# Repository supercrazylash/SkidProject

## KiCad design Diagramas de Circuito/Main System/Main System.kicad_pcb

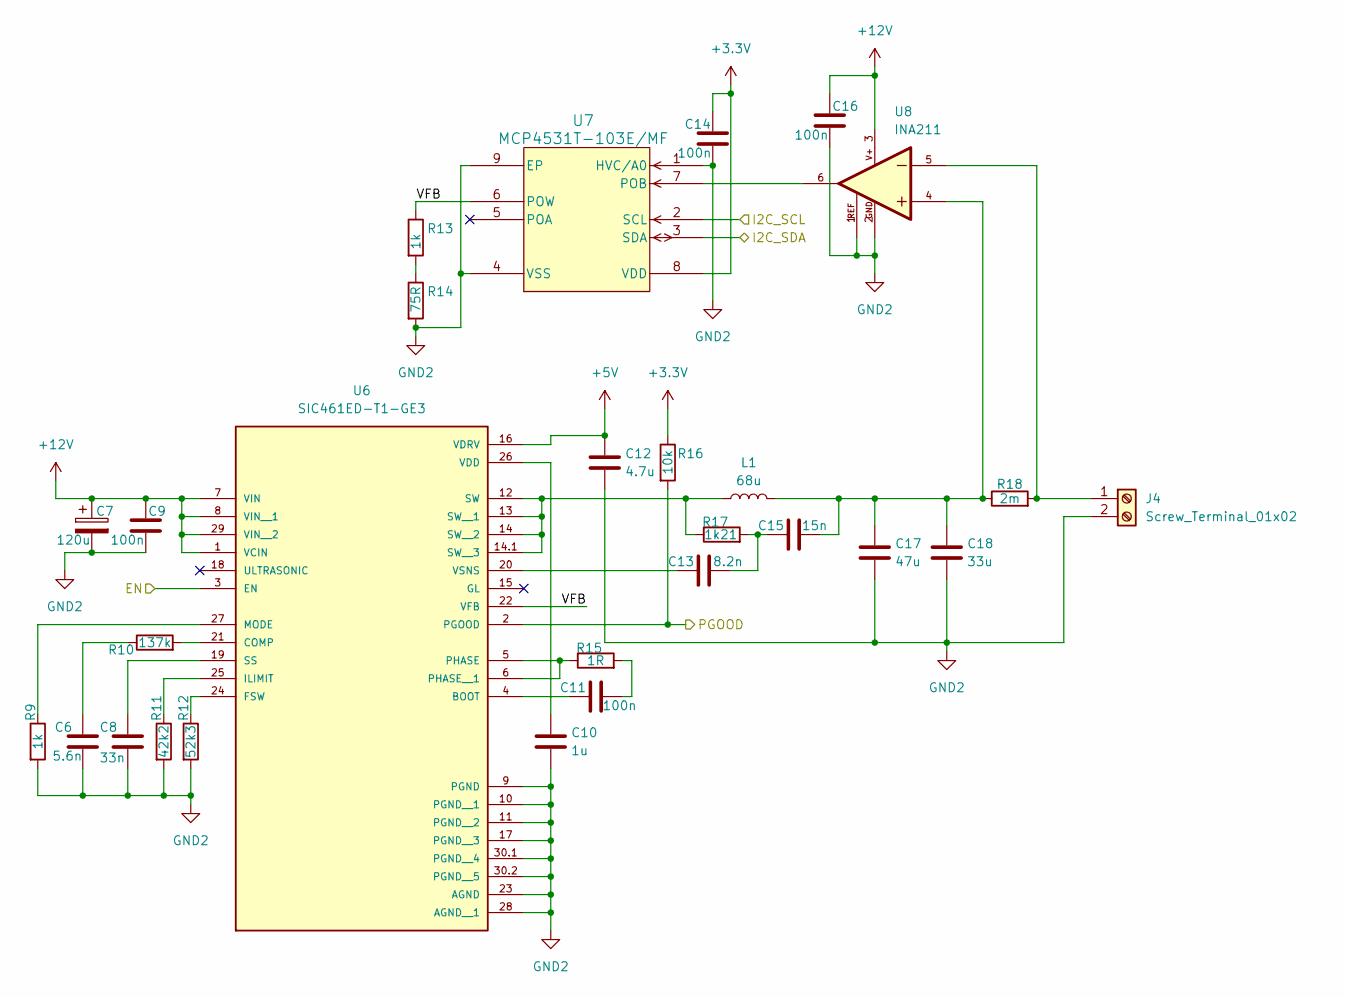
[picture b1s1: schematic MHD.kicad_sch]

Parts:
C6: 5.6n; C_0402_1005Metric; DIGIKEY_PN 311-3773-1-ND
C7: 120u; CP_Radial_D10.0mm_P5.00mm; DIGIKEY_PN 732-11923-1-ND
C8: 33n; C_0402_1005Metric; DIGIKEY_PN 13-CC0402JRX7R9BB333CT-ND
C9, C11, C14, C16: 100n; C_0603_1608Metric; DIGIKEY_PN 1276-1033-1-ND
C10: 1u; C_0805_2012Metric; DIGIKEY_PN 1276-1029-1-ND
C12: 4.7u; C_0603_1608Metric; DIGIKEY_PN 1276-1784-1-ND
C13: 8.2n; C_0603_1608Metric; DIGIKEY_PN 399-C0603C822K5RACTUCT-ND
C15: 15n; C_0402_1005Metric; DIGIKEY_PN 311-3813-1-ND
C17: 47u; C_1210_3225Metric; DIGIKEY_PN 490-10531-1-ND
C18: 33u; C_1206_3216Metric; DIGIKEY_PN 4713-GMC31X5R336M25NTCT-ND
J4: Screw_Terminal_01x02; TerminalBlock_Phoenix_PT-1,5-2-5.0-H_1x02_P5.00mm_Horizontal; DIGIKEY_PN 277-1667-ND
L1: 68u; L_Pulse_PA4349; DIGIKEY_PN 553-PA4349.683ANLTCT-ND
R9, R13: 1k; R_0402_1005Metric; DIGIKEY_PN P1.0KDCCT-ND
R10: 137k; R_0402_1005Metric; DIGIKEY_PN P137KLCT-ND
R11: 42k2; R_0402_1005Metric; DIGIKEY_PN 311-42.2KLRCT-ND
R12: 52k3; R_0402_1005Metric; DIGIKEY_PN P52.3KLCT-ND
R14: 75R; R_0402_1005Metric; DIGIKEY_PN P75.0LCT-ND
R15: 1R; R_0603_1608Metric; DIGIKEY_PN 311-1.00HRCT-ND
R16: 10k; R_0603_1608Metric; DIGIKEY_PN RMCF0603JT10K0CT-ND
R17: 1k21; R_0402_1005Metric; DIGIKEY_PN P1.21KLCT-ND
R18: 2m; R_2512_6332Metric; DIGIKEY_PN 13-PA2512DKF7W0R002ECT-ND
U6: SIC461ED-T1-GE3; CONV_SIC461ED-T1-GE3; PARTREV M; DIGIKEY_PN SIC461ED-T1-GE3CT-ND
U7: MCP4531T-103E/MF; DFN-8-1EP_3x3mm_P0.5mm_EP1.65x2.38mm; DIGIKEY_PN MCP4531T-103E/MFCT-ND
U8: INA211; SOT-363_SC-70-6; PARTREV J; DIGIKEY_PN 296-41417-1-ND

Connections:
+3.3V: C14.1, R16.1, U7.8 (VDD); also elsewhere on the board
+5V: C12.1, U6.16 (VDRV); also elsewhere on the board
+12V: C7.1, C9.1, C16.1, U6.1 (VCIN), U6.7 (VIN), U6.8 (VIN__1), U6.29 (VIN__2), U8.3; also elsewhere on the board
/Magneto-Hidrodynamic Drive/EN: U6.3 (EN); also elsewhere on the board
/Magneto-Hidrodynamic Drive/PGOOD: R16.2, U6.2 (PGOOD); also elsewhere on the board
/Magneto-Hidrodynamic Drive/VFB: R13.1, U6.22 (VFB), U7.6 (POW)
/Processor/I2C_SCL: U7.2 (SCL); also elsewhere on the board
/Processor/I2C_SDA: U7.3 (SDA); also elsewhere on the board
GND2: C6.2, C7.2, C8.2, C9.2, C10.2, C12.2, C14.2, C16.2, C17.2, C18.2, J4.2, R9.2, R11.2, R12.2, R14.2, U6.9 (PGND), U6.10 (PGND__1), U6.11 (PGND__2), U6.17 (PGND__3), U6.23 (AGND), U6.28 (AGND__1), U6.30.1 (PGND__4), U6.30.2 (PGND__5), U7.1 (HVC/A0), U7.4 (VSS), U7.9 (EP), U8.1, U8.2; also elsewhere on the board
unnamed: C6.1, R10.1
unnamed: C11.2, R15.2
unnamed: C13.2, C15.1, R17.2
unnamed: C15.2, C17.1, C18.1, L1.2, R18.1, U8.4
unnamed: J4.1, R18.2, U8.5
unnamed: R13.2, R14.1
unnamed: C11.1, U6.4 (BOOT)
unnamed: R10.2, U6.21 (COMP)
unnamed: R12.1, U6.24 (FSW)
unnamed: R11.1, U6.25 (ILIMIT)
unnamed: R9.1, U6.27 (MODE)
unnamed: R15.1, U6.5 (PHASE), U6.6 (PHASE__1)
unnamed: C8.1, U6.19 (SS)
unnamed: L1.1, R17.1, U6.12 (SW), U6.13 (SW__1), U6.14 (SW__2), U6.14.1 (SW__3)
unnamed: C10.1, U6.26 (VDD)
unnamed: C13.1, U6.20 (VSNS)
unnamed: U7.7 (POB), U8.6

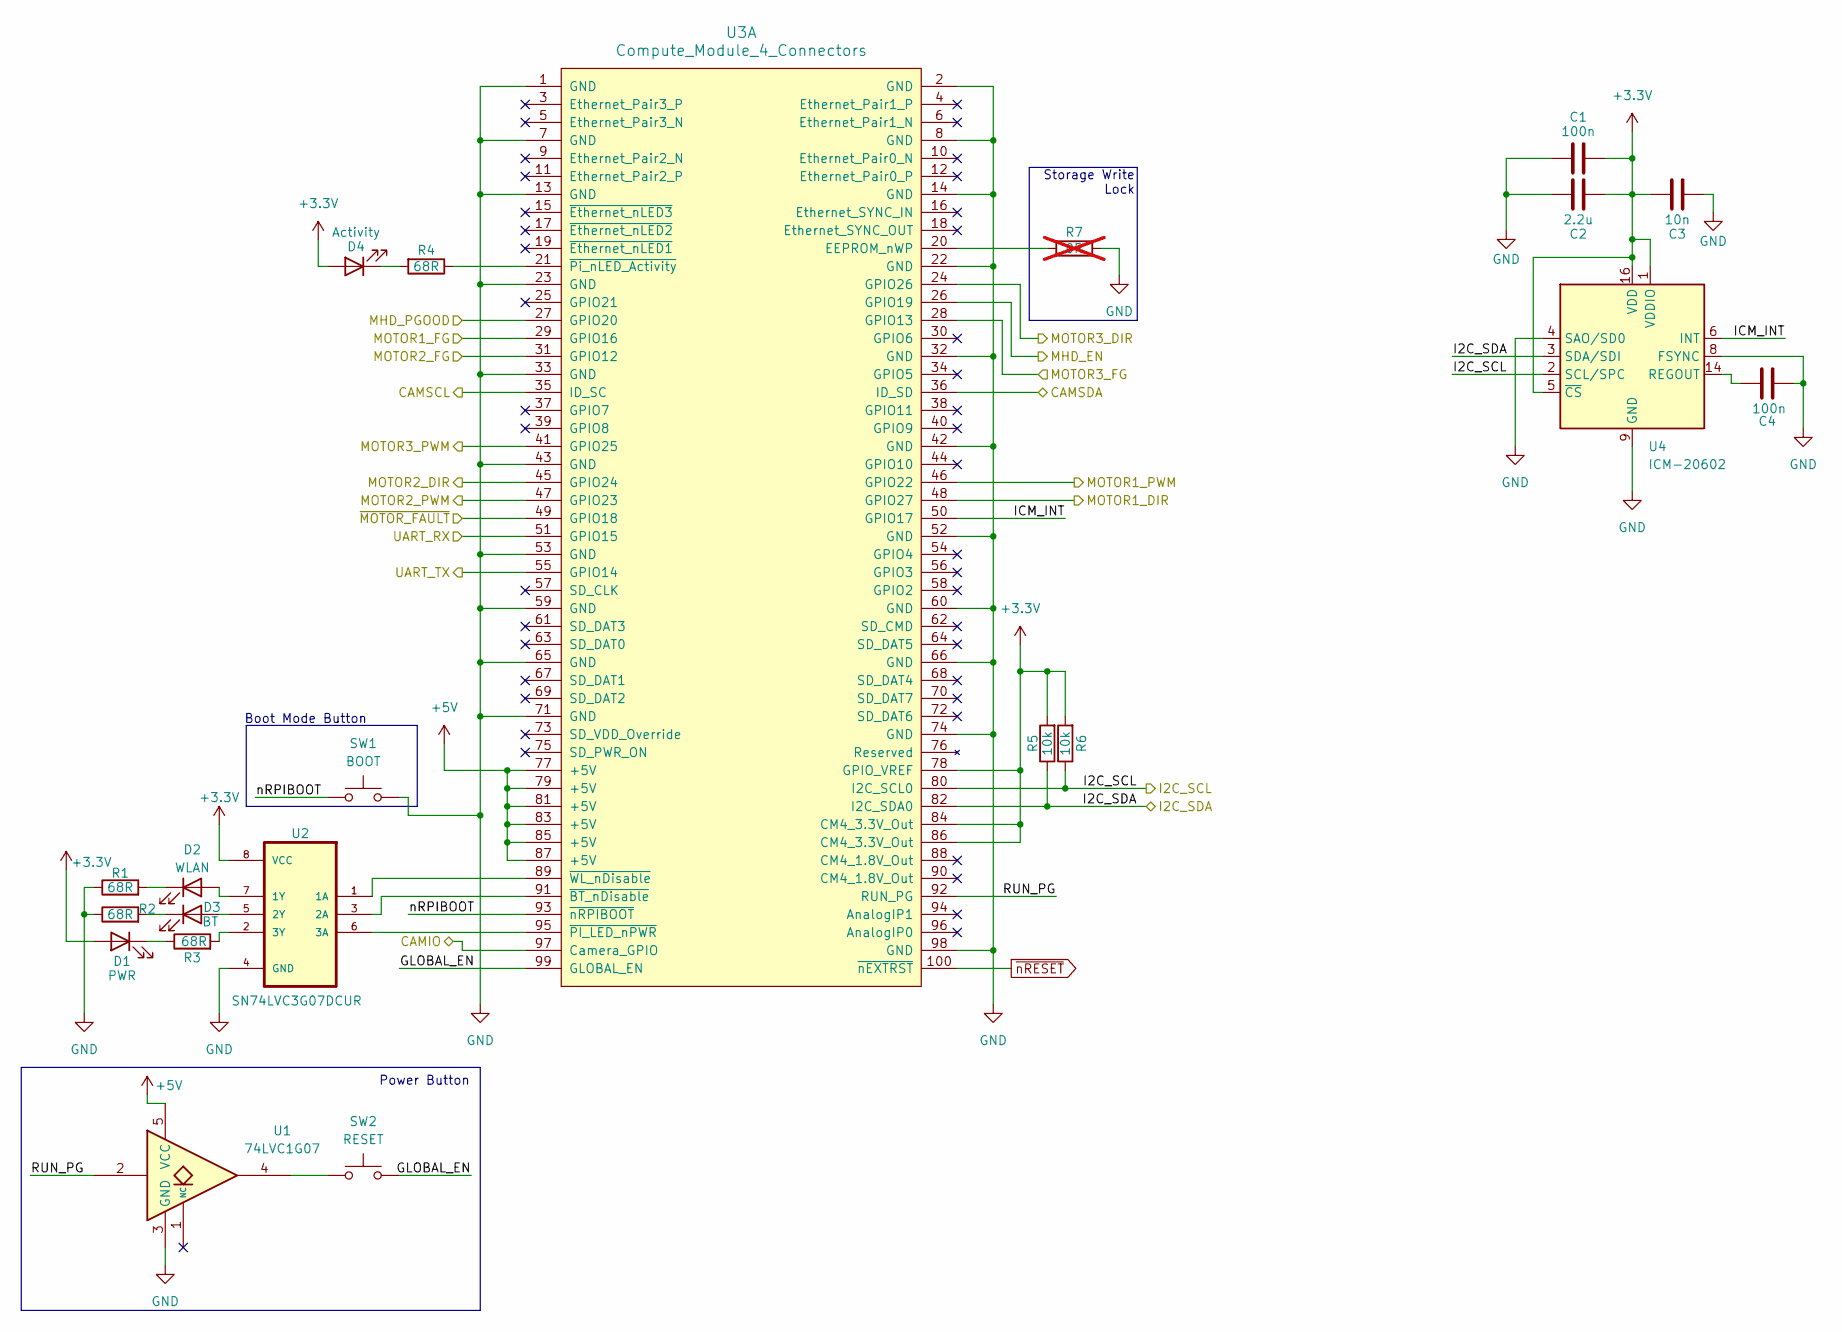
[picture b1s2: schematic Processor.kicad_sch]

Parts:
C1, C4: 100n; C_0603_1608Metric; DIGIKEY_PN 1276-1033-1-ND
C2: 2.2u; C_0603_1608Metric; DIGIKEY_PN 1276-1040-1-ND
C3: 10n; C_0402_1005Metric; DIGIKEY_PN 1276-1028-1-ND
D1: PWR; LED_0603_1608Metric; DIGIKEY_PN 732-4978-1-ND
D2: WLAN; LED_0603_1608Metric; DIGIKEY_PN 732-4980-1-ND
D3: BT; LED_0603_1608Metric; DIGIKEY_PN 732-4980-1-ND
D4: Activity; LED_0603_1608Metric; DIGIKEY_PN 732-4980-1-ND
R1, R2, R3, R4: 68R; R_0402_1005Metric; DIGIKEY_PN P68.0LCT-ND
R5, R6: 10k; R_0603_1608Metric; DIGIKEY_PN RMCF0603JT10K0CT-ND
R7: 0R; R_0402_1005Metric; DIGIKEY_PN P0.0JCT-ND; not fitted
SW1: BOOT; SW_SPST_PTS647_Sx38; DIGIKEY_PN PTS647SM38SMTR2LFSCT-ND
SW2: RESET; SW_SPST_PTS647_Sx38; DIGIKEY_PN PTS647SM38SMTR2LFSCT-ND
U1: 74LVC1G07; SOT-23-5; DIGIKEY_PN 296-8485-1-ND
U2: SN74LVC3G07DCUR; VSSOP-8_2.3x2mm_P0.5mm; DIGIKEY_PN 296-13283-1-ND
U3: Compute_Module_4_Connectors; Raspberry-Pi-4-Compute-Module; DIGIKEY_PN H11615CT-ND
U4: ICM-20602; LGA-16_3x3mm_P0.5mm_LayoutBorder3x5y; DIGIKEY_PN 1428-1060-1-ND

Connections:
+3.3V: C1.2, C2.2, C3.1, D1.2 (A), D4.2 (A), R5.2, R6.2, U2.8 (VCC), U3.78 (GPIO_VREF), U3.84 (CM4_3.3V_Out), U3.86 (CM4_3.3V_Out), U4.1 (VDDIO), U4.5 (~CS), U4.16 (VDD); also elsewhere on the board
+5V: U1.5 (VCC), U3.77 (+5V), U3.79 (+5V), U3.81 (+5V), U3.83 (+5V), U3.85 (+5V), U3.87 (+5V); also elsewhere on the board
/High Speed IO/CAMIO: U3.97 (Camera_GPIO); also elsewhere on the board
/High Speed IO/CAMSCL: U3.35 (ID_SC); also elsewhere on the board
/High Speed IO/CAMSDA: U3.36 (ID_SD); also elsewhere on the board
/High Speed IO/UART_RX: U3.55 (GPIO14); also elsewhere on the board
/High Speed IO/UART_TX: U3.51 (GPIO15); also elsewhere on the board
/Magneto-Hidrodynamic Drive/EN: U3.26 (GPIO19); also elsewhere on the board
/Magneto-Hidrodynamic Drive/PGOOD: U3.27 (GPIO20); also elsewhere on the board
/Processor/GLOBAL_EN: SW2.2, U3.99 (GLOBAL_EN)
/Processor/I2C_SCL: R6.1, U3.80 (I2C_SCL0), U4.2 (SCL/SPC); also elsewhere on the board
/Processor/I2C_SDA: R5.1, U3.82 (I2C_SDA0), U4.3 (SDA/SDI); also elsewhere on the board
/Processor/ICM_INT: U3.50 (GPIO17), U4.6 (INT)
/Processor/MOTOR1_DIR: U3.48 (GPIO27); also elsewhere on the board
/Processor/MOTOR1_FG: U3.29 (GPIO16); also elsewhere on the board
/Processor/MOTOR1_PWM: U3.46 (GPIO22); also elsewhere on the board
/Processor/MOTOR2_DIR: U3.45 (GPIO24); also elsewhere on the board
/Processor/MOTOR2_FG: U3.31 (GPIO12); also elsewhere on the board
/Processor/MOTOR2_PWM: U3.47 (GPIO23); also elsewhere on the board
/Processor/MOTOR3_DIR: U3.24 (GPIO26); also elsewhere on the board
/Processor/MOTOR3_FG: U3.28 (GPIO13); also elsewhere on the board
/Processor/MOTOR3_PWM: U3.41 (GPIO25); also elsewhere on the board
/Processor/RUN_PG: U1.2, U3.92 (RUN_PG)
/Processor/nRPIBOOT: SW1.1, U3.93 (~nRPIBOOT)
/Processor/~MOTOR_FAULT: U3.49 (GPIO18); also elsewhere on the board
GND: C1.1, C2.1, C3.2, C4.2, R1.1, R2.1, R7.2, SW1.2, U1.3 (GND), U2.4 (GND), U3.1 (GND), U3.2 (GND), U3.7 (GND), U3.8 (GND), U3.13 (GND), U3.14 (GND), U3.22 (GND), U3.23 (GND), U3.32 (GND), U3.33 (GND), U3.42 (GND), U3.43 (GND), U3.52 (GND), U3.53 (GND), U3.59 (GND), U3.60 (GND), U3.65 (GND), U3.66 (GND), U3.71 (GND), U3.74 (GND), U3.98 (GND), U4.4 (SAO/SD0), U4.8 (FSYNC), U4.9 (GND), U4.10 (GND), U4.11 (GND), U4.12 (GND), U4.13 (GND), U4.15 (GND); also elsewhere on the board
unnamed: D1.1 (K), R3.1
unnamed: D2.2 (A), U2.7 (1Y)
unnamed: D2.1 (K), R1.2
unnamed: D3.2 (A), U2.5 (2Y)
unnamed: D3.1 (K), R2.2
unnamed: D4.1 (K), R4.2
unnamed: SW2.1, U1.4
unnamed: U2.1 (1A), U3.89 (~WL_nDisable)
unnamed: U2.3 (2A), U3.91 (~BT_nDisable)
unnamed: U2.6 (3A), U3.95 (~PI_LED_nPWR)
unnamed: R3.2, U2.2 (3Y)
unnamed: R7.1, U3.20 (EEPROM_nWP)
unnamed: R4.1, U3.21 (~Pi_nLED_Activity)
unnamed: C4.1, U4.14 (REGOUT)
~nRESET: U3.100 (~nEXTRST); also elsewhere on the board

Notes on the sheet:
Storage Write Lock
Power Button
Boot Mode Button

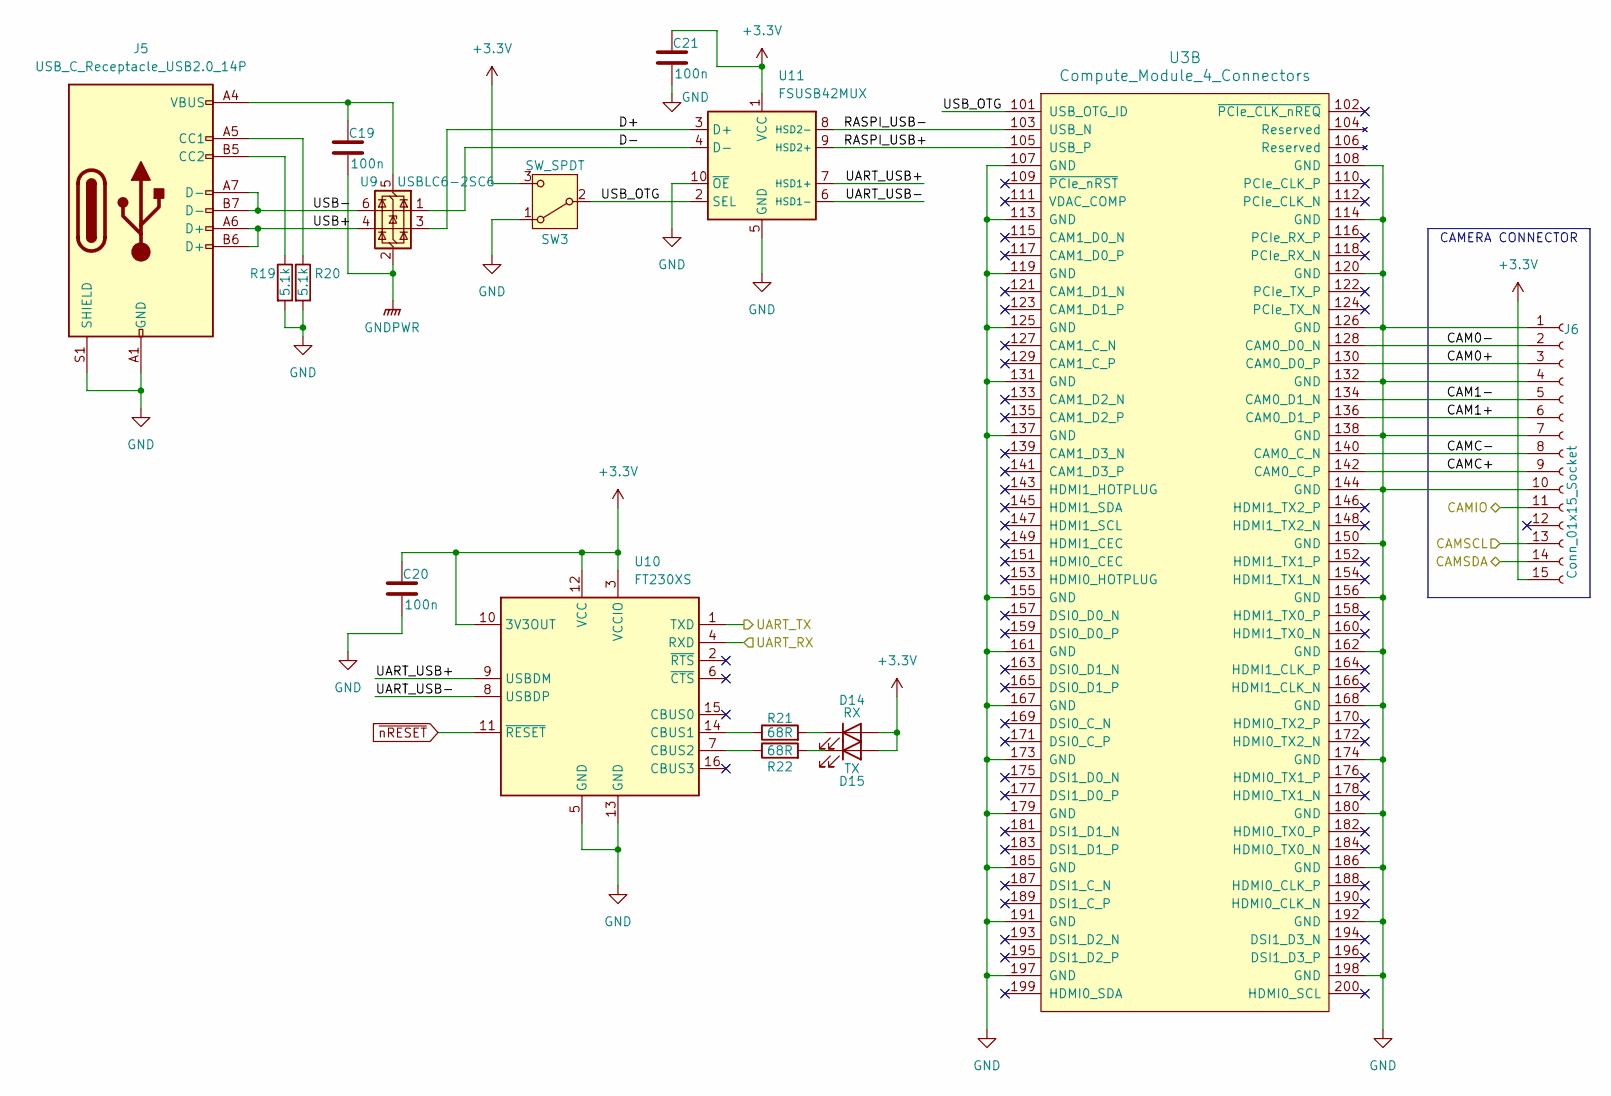
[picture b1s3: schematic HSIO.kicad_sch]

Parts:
C19, C20, C21: 100n; C_0603_1608Metric; DIGIKEY_PN 1276-1033-1-ND
D14: RX; LED_0603_1608Metric; DIGIKEY_PN 732-4980-1-ND
D15: TX; LED_0603_1608Metric; DIGIKEY_PN 732-4980-1-ND
J5: USB_C_Receptacle_USB2.0_14P; USB4120-03-C_GCT; DIGIKEY_PN 2073-USB4120-03-CCT-ND
J6: Conn_01x15_Socket; GCT_FFC3A20-15-G_REVA1; DIGIKEY_PN 2073-FFC3A20-15-GCT-ND
R19, R20: 5.1k; R_0402_1005Metric; DIGIKEY_PN P5.10KLCT-ND
R21, R22: 68R; R_0402_1005Metric; DIGIKEY_PN P68.0LCT-ND
SW3: SW_SPDT; SW_JS102011JCQN; DIGIKEY_PN CKN10721CT-ND
U3: Compute_Module_4_Connectors; Raspberry-Pi-4-Compute-Module; DIGIKEY_PN H11615CT-ND
U9: USBLC6-2SC6; SOT-23-6; DIGIKEY_PN 497-5235-1-ND
U10: FT230XS; SSOP-16_3.9x4.9mm_P0.635mm; DIGIKEY_PN 768-1135-1-ND
U11: FSUSB42MUX; MSOP-10_3x3mm_P0.5mm; DIGIKEY_PN FSUSB42MUXCT-ND

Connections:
+3.3V: C20.1, C21.1, D14.2 (A), D15.2 (A), J6.15, SW3.3 (C), U10.3 (VCCIO), U10.10 (3V3OUT), U10.12 (VCC), U11.1 (VCC); also elsewhere on the board
/High Speed IO/CAM0+: J6.3, U3.130 (CAM0_D0_P)
/High Speed IO/CAM0-: J6.2, U3.128 (CAM0_D0_N)
/High Speed IO/CAM1+: J6.6, U3.136 (CAM0_D1_P)
/High Speed IO/CAM1-: J6.5, U3.134 (CAM0_D1_N)
/High Speed IO/CAMC+: J6.9, U3.142 (CAM0_C_P)
/High Speed IO/CAMC-: J6.8, U3.140 (CAM0_C_N)
/High Speed IO/CAMIO: J6.11; also elsewhere on the board
/High Speed IO/CAMSCL: J6.13; also elsewhere on the board
/High Speed IO/CAMSDA: J6.14; also elsewhere on the board
/High Speed IO/D+: U9.3 (I/O2), U11.3 (D+)
/High Speed IO/D-: U9.1 (I/O1), U11.4 (D-)
/High Speed IO/RASPI_USB+: U3.105 (USB_P), U11.9 (HSD2+)
/High Speed IO/RASPI_USB-: U3.103 (USB_N), U11.8 (HSD2-)
/High Speed IO/UART_RX: U10.4 (RXD); also elsewhere on the board
/High Speed IO/UART_TX: U10.1 (TXD); also elsewhere on the board
/High Speed IO/UART_USB+: U10.9 (USBDM), U11.7 (HSD1+)
/High Speed IO/UART_USB-: U10.8 (USBDP), U11.6 (HSD1-)
/High Speed IO/USB+: J5.A6 (D+), J5.B6 (D+), U9.4 (I/O2)
/High Speed IO/USB-: J5.A7 (D-), J5.B7 (D-), U9.6 (I/O1)
/High Speed IO/USB_OTG: SW3.2 (B), U3.101 (USB_OTG_ID), U11.2 (SEL)
GND: C20.2, C21.2, J5.A1 (GND), J5.A12 (GND), J5.B1 (GND), J5.B12 (GND), J5.S1 (SHIELD), J6.1, J6.4, J6.7, J6.10, R19.2, R20.2, SW3.1 (A), U3.107 (GND), U3.108 (GND), U3.113 (GND), U3.114 (GND), U3.119 (GND), U3.120 (GND), U3.125 (GND), U3.126 (GND), U3.131 (GND), U3.132 (GND), U3.137 (GND), U3.138 (GND), U3.144 (GND), U3.150 (GND), U3.155 (GND), U3.156 (GND), U3.161 (GND), U3.162 (GND), U3.167 (GND), U3.168 (GND), U3.173 (GND), U3.174 (GND), U3.179 (GND), U3.180 (GND), U3.185 (GND), U3.186 (GND), U3.191 (GND), U3.192 (GND), U3.197 (GND), U3.198 (GND), U10.5 (GND), U10.13 (GND), U11.5 (GND), U11.10 (~OE); also elsewhere on the board
GNDPWR: C19.2, U9.2 (GND); also elsewhere on the board
unnamed: D14.1 (K), R21.2
unnamed: D15.1 (K), R22.2
unnamed: J5.A5 (CC1), R20.1
unnamed: J5.B5 (CC2), R19.1
unnamed: C19.1, J5.A4 (VBUS), J5.A9 (VBUS), J5.B4 (VBUS), J5.B9 (VBUS), U9.5 (VBUS)
unnamed: R21.1, U10.14 (CBUS1)
unnamed: R22.1, U10.7 (CBUS2)
~nRESET: U10.11 (~RESET); also elsewhere on the board

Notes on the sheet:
CAMERA CONNECTOR

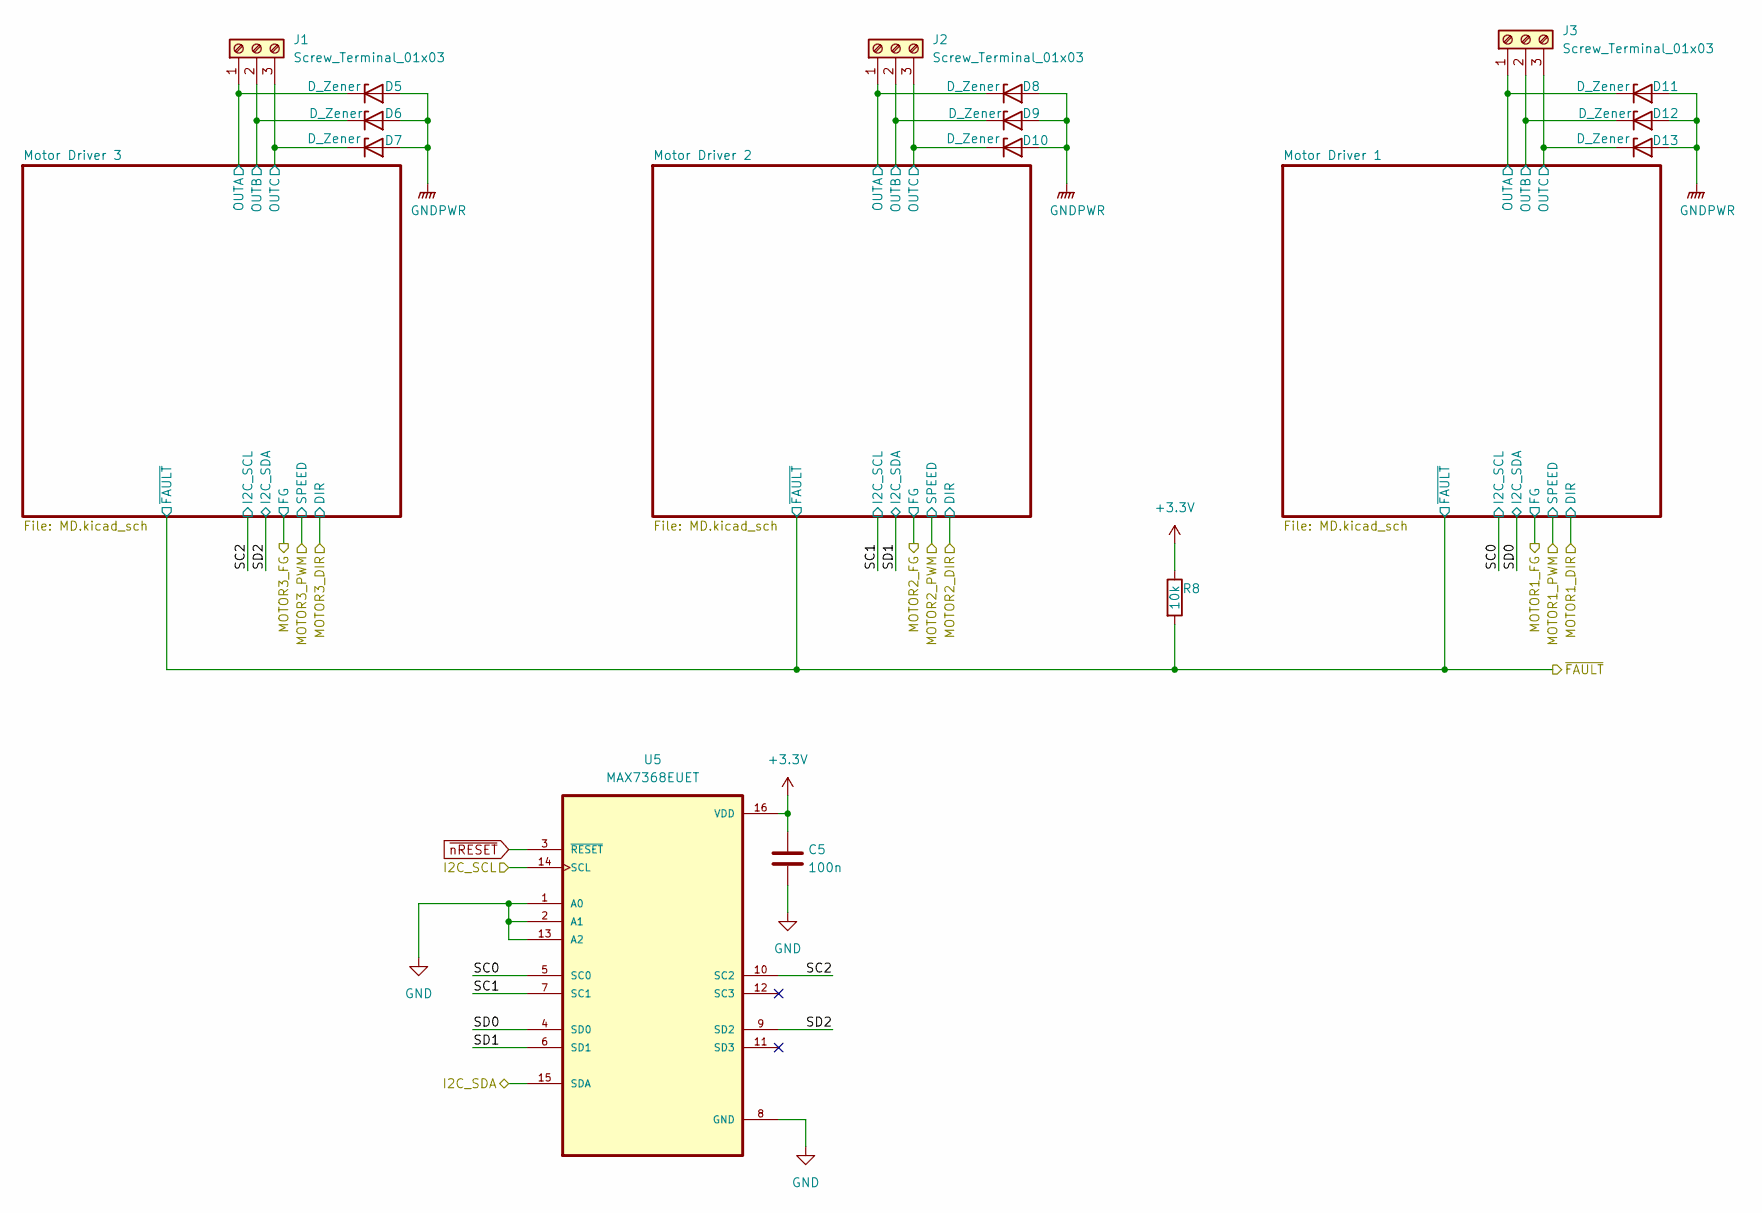
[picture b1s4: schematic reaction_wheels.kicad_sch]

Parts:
C5: 100n; C_0603_1608Metric; DIGIKEY_PN 1276-1033-1-ND
D5, D6, D7, D8, D9, D10, D11, D12, D13: D_Zener; D_SMB; DIGIKEY_PN SMBJ10A-FDICT-ND
J1, J2, J3: Screw_Terminal_01x03; TerminalBlock_Phoenix_PT-1,5-3-5.0-H_1x03_P5.00mm_Horizontal; DIGIKEY_PN 277-1578-ND
R8: 10k; R_0603_1608Metric; DIGIKEY_PN RMCF0603JT10K0CT-ND
U5: MAX7368EUET; TSSOP-16_4.4x5mm_P0.65mm; DIGIKEY_PN MAX7368EUE+-ND

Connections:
+3.3V: C5.1, R8.1, U5.16 (VDD); also elsewhere on the board
/Processor/I2C_SCL: U5.14 (SCL); also elsewhere on the board
/Processor/I2C_SDA: U5.15 (SDA); also elsewhere on the board
/Processor/~MOTOR_FAULT: R8.2; also elsewhere on the board
/Reaction Wheels/Motor Driver 1/OUTA: D11.1 (K), J3.1; also elsewhere on the board
/Reaction Wheels/Motor Driver 1/OUTB: D12.1 (K), J3.2; also elsewhere on the board
/Reaction Wheels/Motor Driver 1/OUTC: D13.1 (K), J3.3; also elsewhere on the board
/Reaction Wheels/Motor Driver 2/OUTA: D8.1 (K), J2.1; also elsewhere on the board
/Reaction Wheels/Motor Driver 2/OUTB: D9.1 (K), J2.2; also elsewhere on the board
/Reaction Wheels/Motor Driver 2/OUTC: D10.1 (K), J2.3; also elsewhere on the board
/Reaction Wheels/Motor Driver 3/OUTA: D5.1 (K), J1.1; also elsewhere on the board
/Reaction Wheels/Motor Driver 3/OUTB: D6.1 (K), J1.2; also elsewhere on the board
/Reaction Wheels/Motor Driver 3/OUTC: D7.1 (K), J1.3; also elsewhere on the board
/Reaction Wheels/SC0: U5.5 (SC0); also elsewhere on the board
/Reaction Wheels/SC1: U5.7 (SC1); also elsewhere on the board
/Reaction Wheels/SC2: U5.10 (SC2); also elsewhere on the board
/Reaction Wheels/SD0: U5.4 (SD0); also elsewhere on the board
/Reaction Wheels/SD1: U5.6 (SD1); also elsewhere on the board
/Reaction Wheels/SD2: U5.9 (SD2); also elsewhere on the board
GND: C5.2, U5.1 (A0), U5.2 (A1), U5.8 (GND), U5.13 (A2); also elsewhere on the board
GNDPWR: D5.2 (A), D6.2 (A), D7.2 (A), D8.2 (A), D9.2 (A), D10.2 (A), D11.2 (A), D12.2 (A), D13.2 (A); also elsewhere on the board
~nRESET: U5.3 (~RESET); also elsewhere on the board

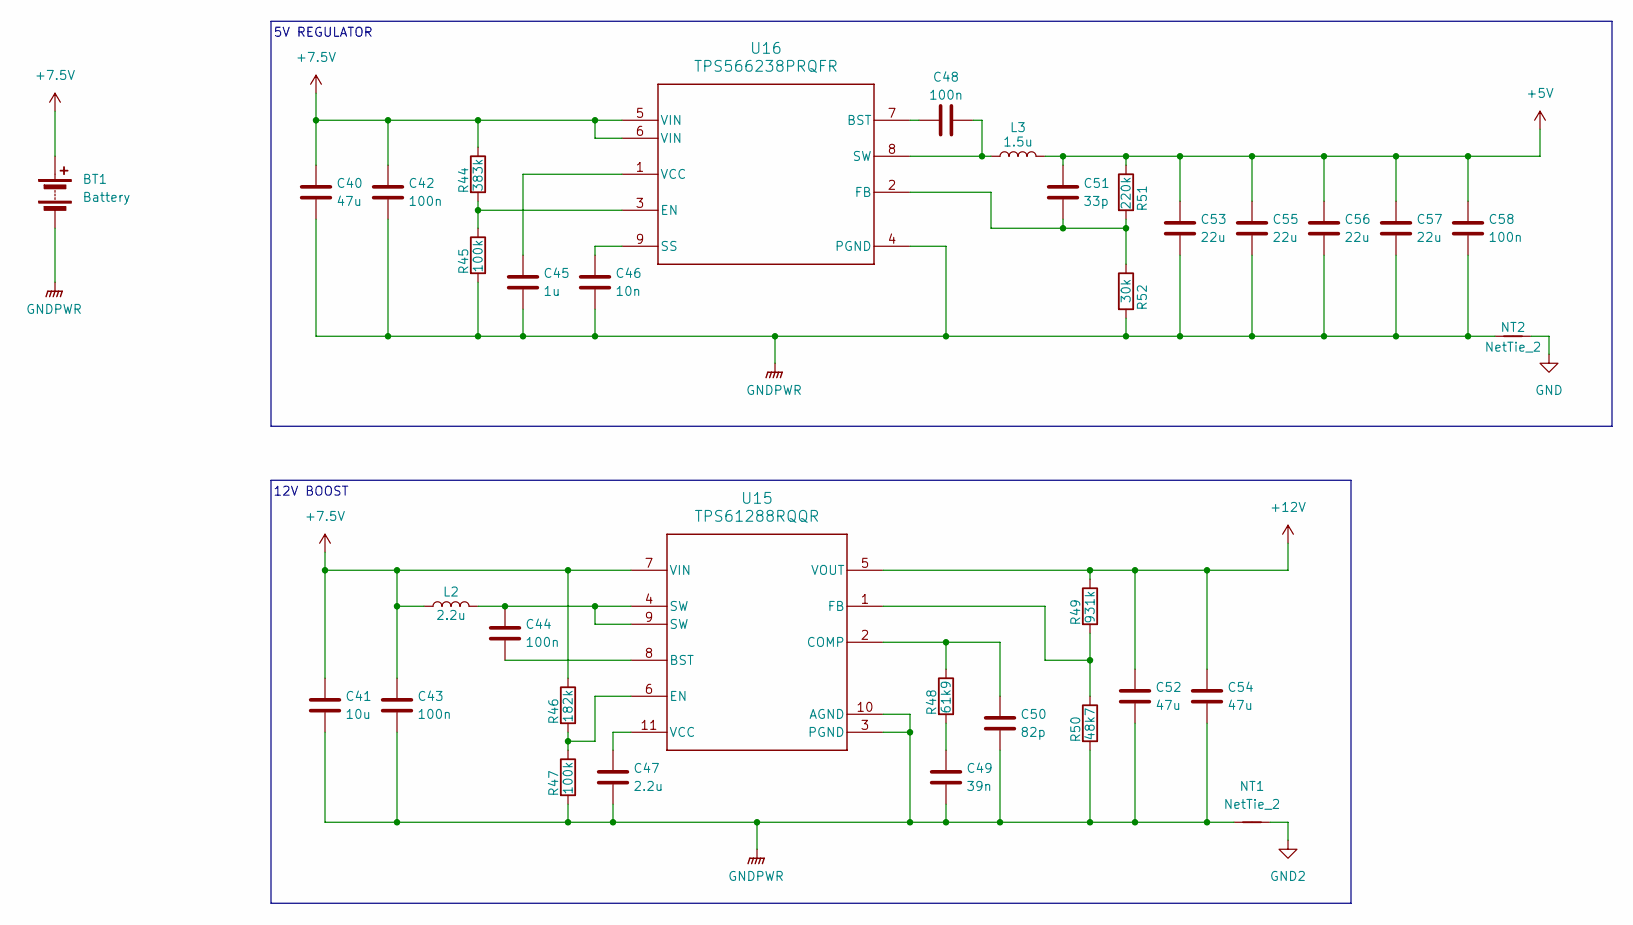
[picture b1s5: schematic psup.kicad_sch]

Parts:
BT1: Battery; DEANS; DIGIKEY_PN 1568-1659-ND
C40, C52, C54: 47u; C_1210_3225Metric; DIGIKEY_PN 490-10531-1-ND
C41: 10u; C_0805_2012Metric; DIGIKEY_PN 1276-6455-1-ND
C42, C43, C44, C48, C58: 100n; C_0603_1608Metric; DIGIKEY_PN 1276-1033-1-ND
C45: 1u; C_0805_2012Metric; DIGIKEY_PN 1276-1029-1-ND
C46: 10n; C_0402_1005Metric; DIGIKEY_PN 1276-1028-1-ND
C47: 2.2u; C_0603_1608Metric; DIGIKEY_PN 1276-1040-1-ND
C49: 39n; C_0603_1608Metric; DIGIKEY_PN 1276-2055-1-ND
C50: 82p; C_0402_1005Metric; DIGIKEY_PN 311-1023-1-ND
C51: 33p; C_0402_1005Metric; DIGIKEY_PN 1276-1272-1-ND
C53, C55, C56, C57: 22u; C_1206_3216Metric; DIGIKEY_PN 1276-3047-1-ND
L2: 2.2u; IND_IHLP-5050CE-01_VIS; DIGIKEY_PN 541-1019-1-ND
L3: 1.5u; IND_-1R5MC_SUM; DIGIKEY_PN 308-2497-1-ND
NT1, NT2: NetTie_2; NetTie-2_SMD_Pad2.0mm
R44: 383k; R_0402_1005Metric; DIGIKEY_PN P383KLCT-ND
R45, R47: 100k; R_0603_1608Metric; DIGIKEY_PN P100KHCT-ND
R46: 182k; R_0402_1005Metric; DIGIKEY_PN P182KLCT-ND
R48: 61k9; R_0402_1005Metric; DIGIKEY_PN P61.9KLCT-ND
R49: 931k; R_0402_1005Metric; DIGIKEY_PN P931KLCT-ND
R50: 48k7; R_0402_1005Metric; DIGIKEY_PN P48.7KLCT-ND
R51: 220k; R_0402_1005Metric; DIGIKEY_PN P220KLCT-ND
R52: 30k; R_0402_1005Metric; DIGIKEY_PN P30.0KLCT-ND
U15: TPS61288RQQR; RQQ0011A-MFG; DIGIKEY_PN 296-TPS61288RQQRCT-ND
U16: TPS566238PRQFR; RQF0009A; DIGIKEY_PN 296-TPS566238PRQFRCT-ND

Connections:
+5V: C51.1, C53.1, C55.1, C56.1, C57.1, C58.1, L3.2, R51.1; also elsewhere on the board
+7.5V: BT1.1 (+), C40.1, C41.1, C42.1, C43.1, L2.1, R44.1, R46.1, U15.7 (VIN), U16.5 (VIN), U16.6 (VIN); also elsewhere on the board
+12V: C52.1, C54.1, R49.1, U15.5 (VOUT); also elsewhere on the board
GND: NT2.2; also elsewhere on the board
GND2: NT1.2; also elsewhere on the board
GNDPWR: BT1.2 (-), C40.2, C41.2, C42.2, C43.2, C45.2, C46.2, C47.2, C49.2, C50.2, C52.2, C53.2, C54.2, C55.2, C56.2, C57.2, C58.2, NT1.1, NT2.1, R45.2, R47.2, R50.2, R52.2, U15.3 (PGND), U15.10 (AGND), U16.4 (PGND); also elsewhere on the board
unnamed: C44.1, L2.2, U15.4 (SW), U15.9 (SW)
unnamed: C49.1, R48.2
unnamed: C44.2, U15.8 (BST)
unnamed: C50.1, R48.1, U15.2 (COMP)
unnamed: R46.2, R47.1, U15.6 (EN)
unnamed: R49.2, R50.1, U15.1 (FB)
unnamed: C47.1, U15.11 (VCC)
unnamed: C48.1, U16.7 (BST)
unnamed: R44.2, R45.1, U16.3 (EN)
unnamed: C51.2, R51.2, R52.1, U16.2 (FB)
unnamed: C46.1, U16.9 (SS)
unnamed: C48.2, L3.1, U16.8 (SW)
unnamed: C45.1, U16.1 (VCC)

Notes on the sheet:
5V REGULATOR
12V BOOST

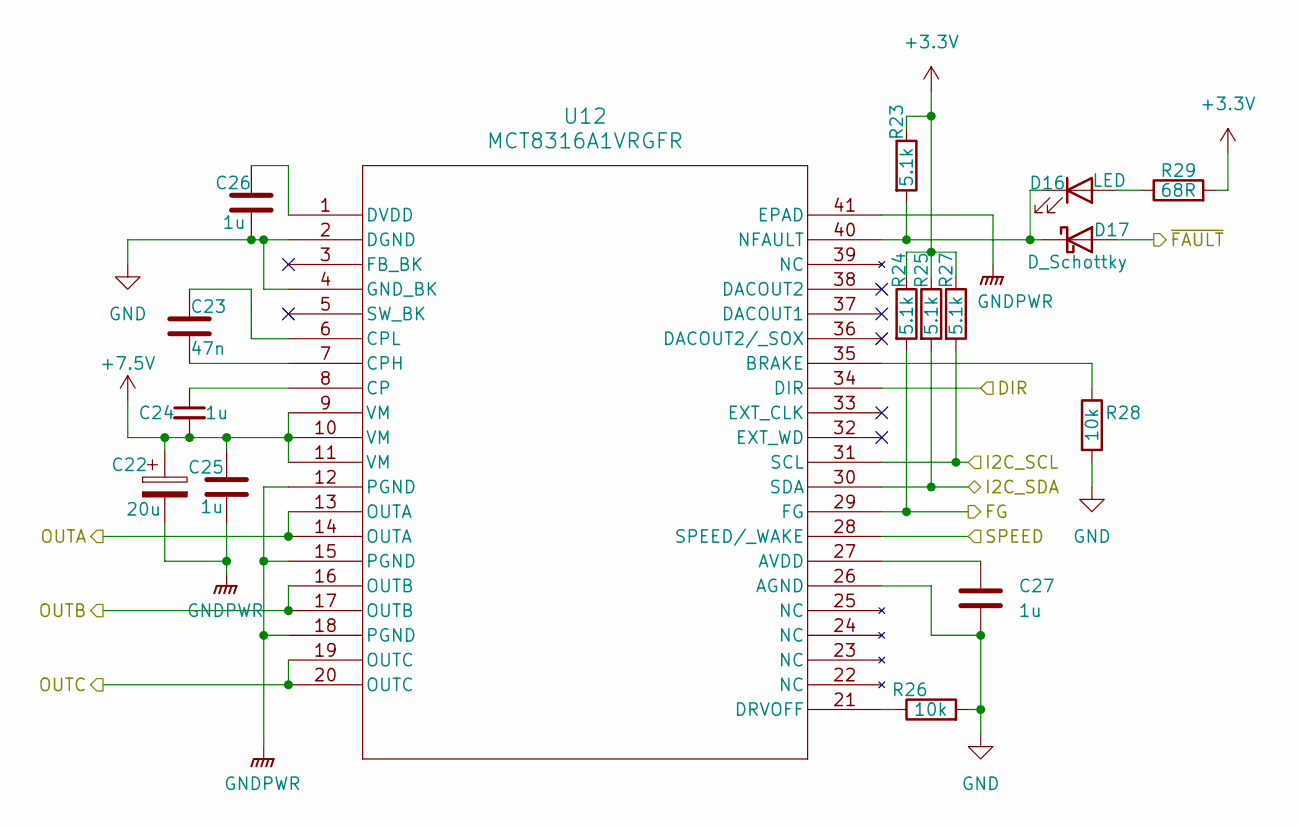
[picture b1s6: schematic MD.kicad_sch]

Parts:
C22: 20u; CP_Radial_D10.0mm_P5.00mm; DIGIKEY_PN 565-EGXF351ELL200MJ25S-ND
C23: 47n; C_0402_1005Metric; DIGIKEY_PN 445-6897-1-ND
C24, C25, C26, C27: 1u; C_0805_2012Metric; DIGIKEY_PN 1276-1029-1-ND
D16: LED; LED_0603_1608Metric; DIGIKEY_PN 732-4978-1-ND
D17: D_Schottky; D_SOD-323; DIGIKEY_PN 3757-SD103AWS_R1_00001CT-ND
R23, R24, R25, R27: 5.1k; R_0402_1005Metric; DIGIKEY_PN P5.10KLCT-ND
R26, R28: 10k; R_0603_1608Metric; DIGIKEY_PN RMCF0603JT10K0CT-ND
R29: 68R; R_0402_1005Metric; DIGIKEY_PN P68.0LCT-ND
U12: MCT8316A1VRGFR; VQFN40_RGF_TEX; DIGIKEY_PN 296-MCT8316A1VRGFRCT-ND

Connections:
+3.3V: R23.1, R24.1, R25.1, R27.1, R29.2; also elsewhere on the board
+7.5V: C22.1, C24.2, C25.1, U12.9 (VM), U12.10 (VM), U12.11 (VM); also elsewhere on the board
/Processor/MOTOR1_DIR: U12.34 (DIR); also elsewhere on the board
/Processor/MOTOR1_FG: R24.2, U12.29 (FG); also elsewhere on the board
/Processor/MOTOR1_PWM: U12.28 (SPEED/_WAKE); also elsewhere on the board
/Processor/~MOTOR_FAULT: D17.2 (A); also elsewhere on the board
/Reaction Wheels/Motor Driver 1/OUTA: U12.13 (OUTA), U12.14 (OUTA); also elsewhere on the board
/Reaction Wheels/Motor Driver 1/OUTB: U12.16 (OUTB), U12.17 (OUTB); also elsewhere on the board
/Reaction Wheels/Motor Driver 1/OUTC: U12.19 (OUTC), U12.20 (OUTC); also elsewhere on the board
/Reaction Wheels/SC0: R27.2, U12.31 (SCL); also elsewhere on the board
/Reaction Wheels/SD0: R25.2, U12.30 (SDA); also elsewhere on the board
GND: C26.2, C27.2, R26.2, R28.2, U12.2 (DGND), U12.4 (GND_BK), U12.26 (AGND); also elsewhere on the board
GNDPWR: C22.2, C25.2, U12.12 (PGND), U12.15 (PGND), U12.18 (PGND), U12.41 (EPAD); also elsewhere on the board
unnamed: D16.2 (A), R29.1
unnamed: D16.1 (K), D17.1 (K), R23.2, U12.40 (NFAULT)
unnamed: C27.1, U12.27 (AVDD)
unnamed: R28.1, U12.35 (BRAKE)
unnamed: C24.1, U12.8 (CP)
unnamed: C23.2, U12.7 (CPH)
unnamed: C23.1, U12.6 (CPL)
unnamed: R26.1, U12.21 (DRVOFF)
unnamed: C26.1, U12.1 (DVDD)

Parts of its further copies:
C28, C34: 20u; CP_Radial_D10.0mm_P5.00mm; DIGIKEY_PN 565-EGXF351ELL200MJ25S-ND
C29, C35: 47n; C_0402_1005Metric; DIGIKEY_PN 445-6897-1-ND
C30, C31, C32, C33, C36, C37, C38, C39: 1u; C_0805_2012Metric; DIGIKEY_PN 1276-1029-1-ND
D18, D20: LED; LED_0603_1608Metric; DIGIKEY_PN 732-4978-1-ND
D19, D21: D_Schottky; D_SOD-323; DIGIKEY_PN 3757-SD103AWS_R1_00001CT-ND
R30, R31, R32, R34, R37, R38, R39, R41: 5.1k; R_0402_1005Metric; DIGIKEY_PN P5.10KLCT-ND
R33, R35, R40, R42: 10k; R_0603_1608Metric; DIGIKEY_PN RMCF0603JT10K0CT-ND
R36, R43: 68R; R_0402_1005Metric; DIGIKEY_PN P68.0LCT-ND
U13, U14: MCT8316A1VRGFR; VQFN40_RGF_TEX; DIGIKEY_PN 296-MCT8316A1VRGFRCT-ND

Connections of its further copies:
+3.3V: R30.1, R31.1, R32.1, R34.1, R36.2, R37.1, R38.1, R39.1, R41.1, R43.2; also elsewhere on the board
+7.5V: C28.1, C30.2, C31.1, C34.1, C36.2, C37.1, U13.9 (VM), U13.10 (VM), U13.11 (VM), U14.9 (VM), U14.10 (VM), U14.11 (VM); also elsewhere on the board
/Processor/MOTOR2_DIR: U13.34 (DIR); also elsewhere on the board
/Processor/MOTOR2_FG: R31.2, U13.29 (FG); also elsewhere on the board
/Processor/MOTOR2_PWM: U13.28 (SPEED/_WAKE); also elsewhere on the board
/Processor/MOTOR3_DIR: U14.34 (DIR); also elsewhere on the board
/Processor/MOTOR3_FG: R38.2, U14.29 (FG); also elsewhere on the board
/Processor/MOTOR3_PWM: U14.28 (SPEED/_WAKE); also elsewhere on the board
/Processor/~MOTOR_FAULT: D19.2 (A), D21.2 (A); also elsewhere on the board
/Reaction Wheels/Motor Driver 2/OUTA: U13.13 (OUTA), U13.14 (OUTA); also elsewhere on the board
/Reaction Wheels/Motor Driver 2/OUTB: U13.16 (OUTB), U13.17 (OUTB); also elsewhere on the board
/Reaction Wheels/Motor Driver 2/OUTC: U13.19 (OUTC), U13.20 (OUTC); also elsewhere on the board
/Reaction Wheels/Motor Driver 3/OUTA: U14.13 (OUTA), U14.14 (OUTA); also elsewhere on the board
/Reaction Wheels/Motor Driver 3/OUTB: U14.16 (OUTB), U14.17 (OUTB); also elsewhere on the board
/Reaction Wheels/Motor Driver 3/OUTC: U14.19 (OUTC), U14.20 (OUTC); also elsewhere on the board
/Reaction Wheels/SC1: R34.2, U13.31 (SCL); also elsewhere on the board
/Reaction Wheels/SC2: R41.2, U14.31 (SCL); also elsewhere on the board
/Reaction Wheels/SD1: R32.2, U13.30 (SDA); also elsewhere on the board
/Reaction Wheels/SD2: R39.2, U14.30 (SDA); also elsewhere on the board
GND: C32.2, C33.2, C38.2, C39.2, R33.2, R35.2, R40.2, R42.2, U13.2 (DGND), U13.4 (GND_BK), U13.26 (AGND), U14.2 (DGND), U14.4 (GND_BK), U14.26 (AGND); also elsewhere on the board
GNDPWR: C28.2, C31.2, C34.2, C37.2, U13.12 (PGND), U13.15 (PGND), U13.18 (PGND), U13.41 (EPAD), U14.12 (PGND), U14.15 (PGND), U14.18 (PGND), U14.41 (EPAD); also elsewhere on the board
unnamed: D18.2 (A), R36.1
unnamed: D18.1 (K), D19.1 (K), R30.2, U13.40 (NFAULT)
unnamed: D20.2 (A), R43.1
unnamed: D20.1 (K), D21.1 (K), R37.2, U14.40 (NFAULT)
unnamed: C33.1, U13.27 (AVDD)
unnamed: R35.1, U13.35 (BRAKE)
unnamed: C30.1, U13.8 (CP)
unnamed: C29.2, U13.7 (CPH)
unnamed: C29.1, U13.6 (CPL)
unnamed: R33.1, U13.21 (DRVOFF)
unnamed: C32.1, U13.1 (DVDD)
unnamed: C39.1, U14.27 (AVDD)
unnamed: R42.1, U14.35 (BRAKE)
unnamed: C36.1, U14.8 (CP)
unnamed: C35.2, U14.7 (CPH)
unnamed: C35.1, U14.6 (CPL)
unnamed: R40.1, U14.21 (DRVOFF)
unnamed: C38.1, U14.1 (DVDD)
